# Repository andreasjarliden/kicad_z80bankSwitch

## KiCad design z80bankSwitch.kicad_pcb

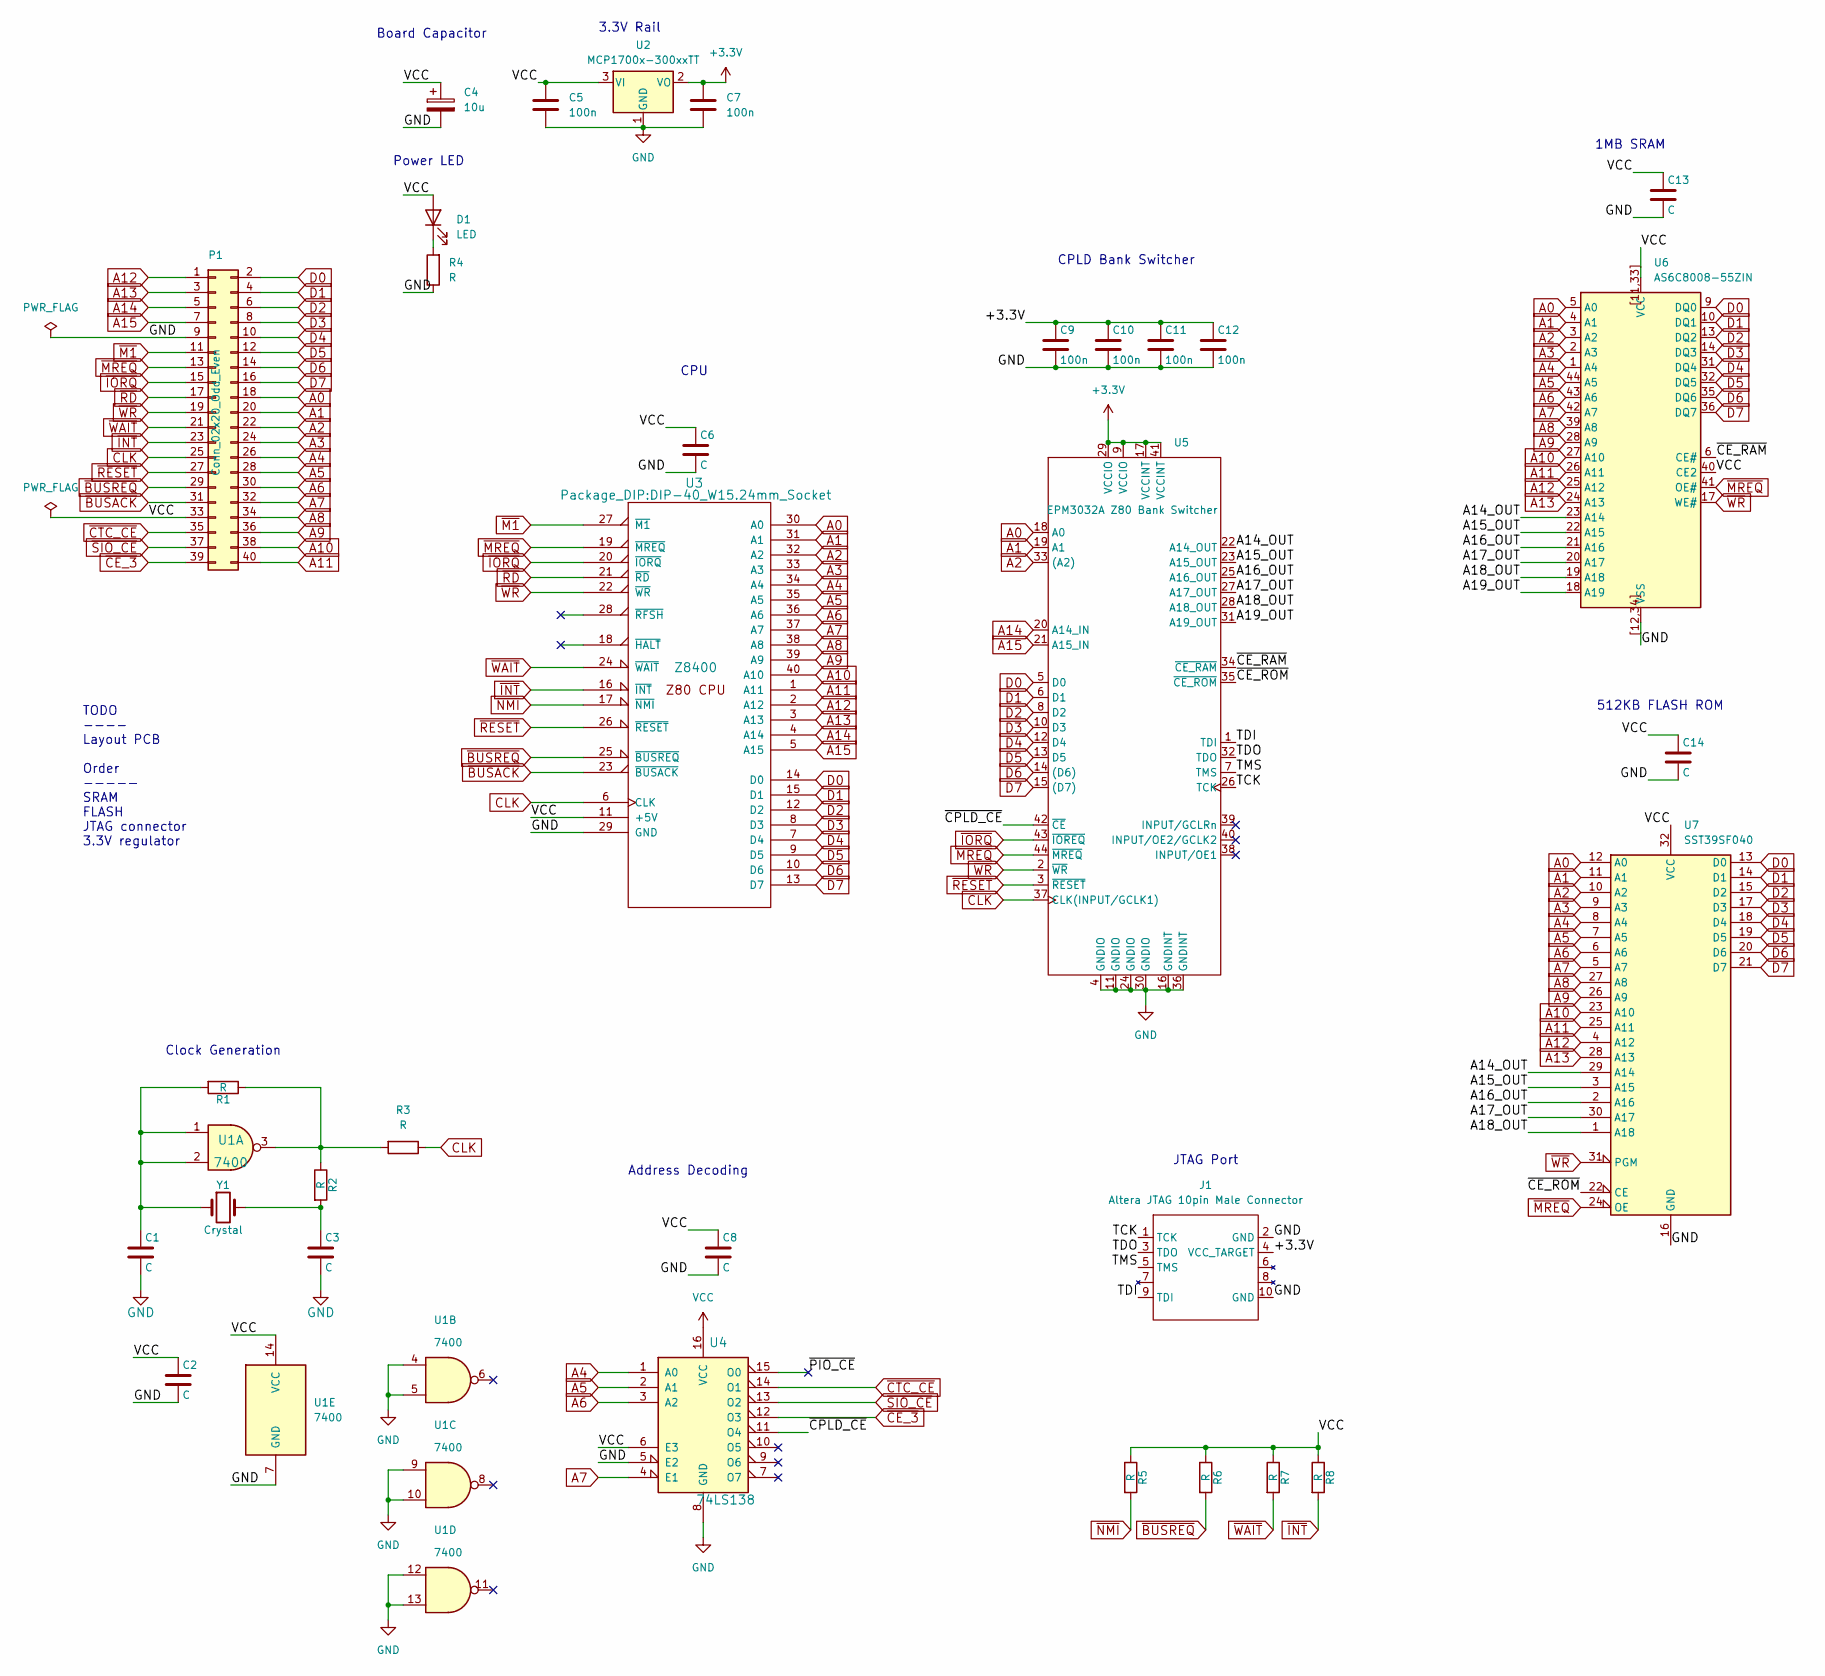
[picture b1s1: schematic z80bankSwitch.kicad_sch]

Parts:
C1, C2, C3, C6, C8, C13, C14: C; C_0805_2012Metric_Pad1.18x1.45mm_HandSolder
C4: 10u; CP_Radial_D10.0mm_P5.00mm
C5, C7, C9, C10, C11, C12: 100n; C_0805_2012Metric_Pad1.18x1.45mm_HandSolder
D1: LED; LED_0805_2012Metric_Pad1.15x1.40mm_HandSolder
J1: Altera JTAG 10pin Male Connector; IDC-Header_2x05_P2.54mm_Vertical
P1: Conn_02x20_Odd_Even; PinHeader_2x20_P2.54mm_Horizontal
R1, R2, R3, R4, R5, R6, R7, R8: R; R_0805_2012Metric_Pad1.20x1.40mm_HandSolder
U1: 7400; DIP-14_W7.62mm_Socket_LongPads
U2: MCP1700x-300xxTT; SOT-23
U3: Z8400; DIP-40_W15.24mm_Socket
U4: 74LS138; DIP-16_W7.62mm_Socket_LongPads
U5: EPM3032A Z80 Bank Switcher; TQFP-44_10x10mm_P0.8mm
U6: AS6C8008-55ZIN; TSOP-II-44_10.16x18.41mm_P0.8mm
U7: SST39SF040; PLCC-32_THT-Socket
Y1: Crystal; Crystal_HC49-4H_Vertical

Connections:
+3.3V: C7.1, C9.1, C10.1, C11.1, C12.1, J1.4 (VCC_TARGET), U2.2 (VO), U5.9 (VCCIO), U5.17 (VCCINT), U5.29 (VCCIO), U5.41 (VCCINT)
/A14_OUT: U5.22 (A14_OUT), U6.23 (A14), U7.29 (A14)
/A15_OUT: U5.23 (A15_OUT), U6.22 (A15), U7.3 (A15)
/A16_OUT: U5.25 (A16_OUT), U6.21 (A16), U7.2 (A16)
/A17_OUT: U5.27 (A17_OUT), U6.20 (A17), U7.30 (A17)
/A18_OUT: U5.28 (A18_OUT), U6.19 (A18), U7.1 (A18)
/A19_OUT: U5.31 (A19_OUT), U6.18 (A19)
/TCK: J1.1 (TCK), U5.26 (TCK)
/TDI: J1.9 (TDI), U5.1 (TDI)
/TDO: J1.3 (TDO), U5.32 (TDO)
/TMS: J1.5 (TMS), U5.7 (TMS)
/~CE_RAM: U5.34 (~CE_RAM), U6.6 (CE#)
/~CE_ROM: U5.35 (~CE_ROM), U7.22 (CE)
/~CPLD_CE: U4.11 (O4), U5.42 (~CE)
/~PIO_CE: U4.15 (O0)
A0: P1.18, U3.30 (A0), U5.18 (A0), U6.5 (A0), U7.12 (A0)
A1: P1.20, U3.31 (A1), U5.19 (A1), U6.4 (A1), U7.11 (A1)
A2: P1.22, U3.32 (A2), U5.33 ((A2)), U6.3 (A2), U7.10 (A2)
A3: P1.24, U3.33 (A3), U6.2 (A3), U7.9 (A3)
A4: P1.26, U3.34 (A4), U4.1 (A0), U6.1 (A4), U7.8 (A4)
A5: P1.28, U3.35 (A5), U4.2 (A1), U6.44 (A5), U7.7 (A5)
A6: P1.30, U3.36 (A6), U4.3 (A2), U6.43 (A6), U7.6 (A6)
A7: P1.32, U3.37 (A7), U4.4 (E1), U6.42 (A7), U7.5 (A7)
A8: P1.34, U3.38 (A8), U6.39 (A8), U7.27 (A8)
A9: P1.36, U3.39 (A9), U6.28 (A9), U7.26 (A9)
A10: P1.38, U3.40 (A10), U6.27 (A10), U7.23 (A10)
A11: P1.40, U3.1 (A11), U6.26 (A11), U7.25 (A11)
A12: P1.1, U3.2 (A12), U6.25 (A12), U7.4 (A12)
A13: P1.3, U3.3 (A13), U6.24 (A13), U7.28 (A13)
A14: P1.5, U3.4 (A14), U5.20 (A14_IN)
A15: P1.7, U3.5 (A15), U5.21 (A15_IN)
CLK: P1.25, R3.1, U3.6 (CLK), U5.37 (CLK(INPUT/GCLK1))
D0: P1.2, U3.14 (D0), U5.5 (D0), U6.9 (DQ0), U7.13 (D0)
D1: P1.4, U3.15 (D1), U5.6 (D1), U6.10 (DQ1), U7.14 (D1)
D2: P1.6, U3.12 (D2), U5.8 (D2), U6.13 (DQ2), U7.15 (D2)
D3: P1.8, U3.8 (D3), U5.10 (D3), U6.14 (DQ3), U7.17 (D3)
D4: P1.10, U3.7 (D4), U5.12 (D4), U6.31 (DQ4), U7.18 (D4)
D5: P1.12, U3.9 (D5), U5.13 (D5), U6.32 (DQ5), U7.19 (D5)
D6: P1.14, U3.10 (D6), U5.14 ((D6)), U6.35 (DQ6), U7.20 (D6)
D7: P1.16, U3.13 (D7), U5.15 ((D7)), U6.36 (DQ7), U7.21 (D7)
GND: C1.2, C2.2, C3.2, C4.2, C5.2, C6.2, C7.2, C8.2, C9.2, C10.2, C11.2, C12.2, C13.2, C14.2, J1.2 (GND), J1.10 (GND), P1.9, R4.1, U1.4, U1.5, U1.7 (GND), U1.9, U1.10, U1.12, U1.13, U2.1 (GND), U3.29 (GND), U4.5 (E2), U4.8 (GND), U5.4 (GNDIO), U5.11 (GNDIO), U5.16 (GNDINT), U5.24 (GNDIO), U5.30 (GNDIO), U5.36 (GNDINT), U6.12 (VSS), U6.34 (VSS), U6.[12,34] (VSS), U7.16 (GND)
unnamed: C1.1, R1.2, U1.1, U1.2, Y1.1
unnamed: C3.1, R2.2, Y1.2
unnamed: D1.1 (K), R4.2
unnamed: R1.1, R2.1, R3.2, U1.3
VCC: C2.1, C4.1, C5.1, C6.1, C8.1, C13.1, C14.1, D1.2 (A), P1.33, R5.1, R6.1, R7.1, R8.1, U1.14 (VCC), U2.3 (VI), U3.11 (+5V), U4.6 (E3), U4.16 (VCC), U6.11 (VCC), U6.33 (VCC), U6.40 (CE2), U6.[11,33] (VCC), U7.32 (VCC)
~BUSACK: P1.31, U3.23 (~BUSACK)
~BUSREQ: P1.29, R6.2, U3.25 (~BUSREQ)
~CE_3: P1.39, U4.12 (O3)
~CTC_CE: P1.35, U4.14 (O1)
~INT: P1.23, R8.2, U3.16 (~INT)
~IORQ: P1.15, U3.20 (~IORQ), U5.43 (~IOREQ)
~M1: P1.11, U3.27 (~M1)
~MREQ: P1.13, U3.19 (~MREQ), U5.44 (~MREQ), U6.41 (OE#), U7.24 (OE)
~NMI: R5.2, U3.17 (~NMI)
~RD: P1.17, U3.21 (~RD)
~RESET: P1.27, U3.26 (~RESET), U5.3 (~RESET)
~SIO_CE: P1.37, U4.13 (O2)
~WAIT: P1.21, R7.2, U3.24 (~WAIT)
~WR: P1.19, U3.22 (~WR), U5.2 (~WR), U6.17 (WE#), U7.31 (PGM)

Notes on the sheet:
TODO ---- Layout PCB Order ----- SRAM FLASH JTAG connector 3.3V regulator
1MB SRAM
Clock Generation
CPLD Bank Switcher
Power LED
CPU
512KB FLASH ROM
3.3V Rail
JTAG Port
Board Capacitor
Address Decoding

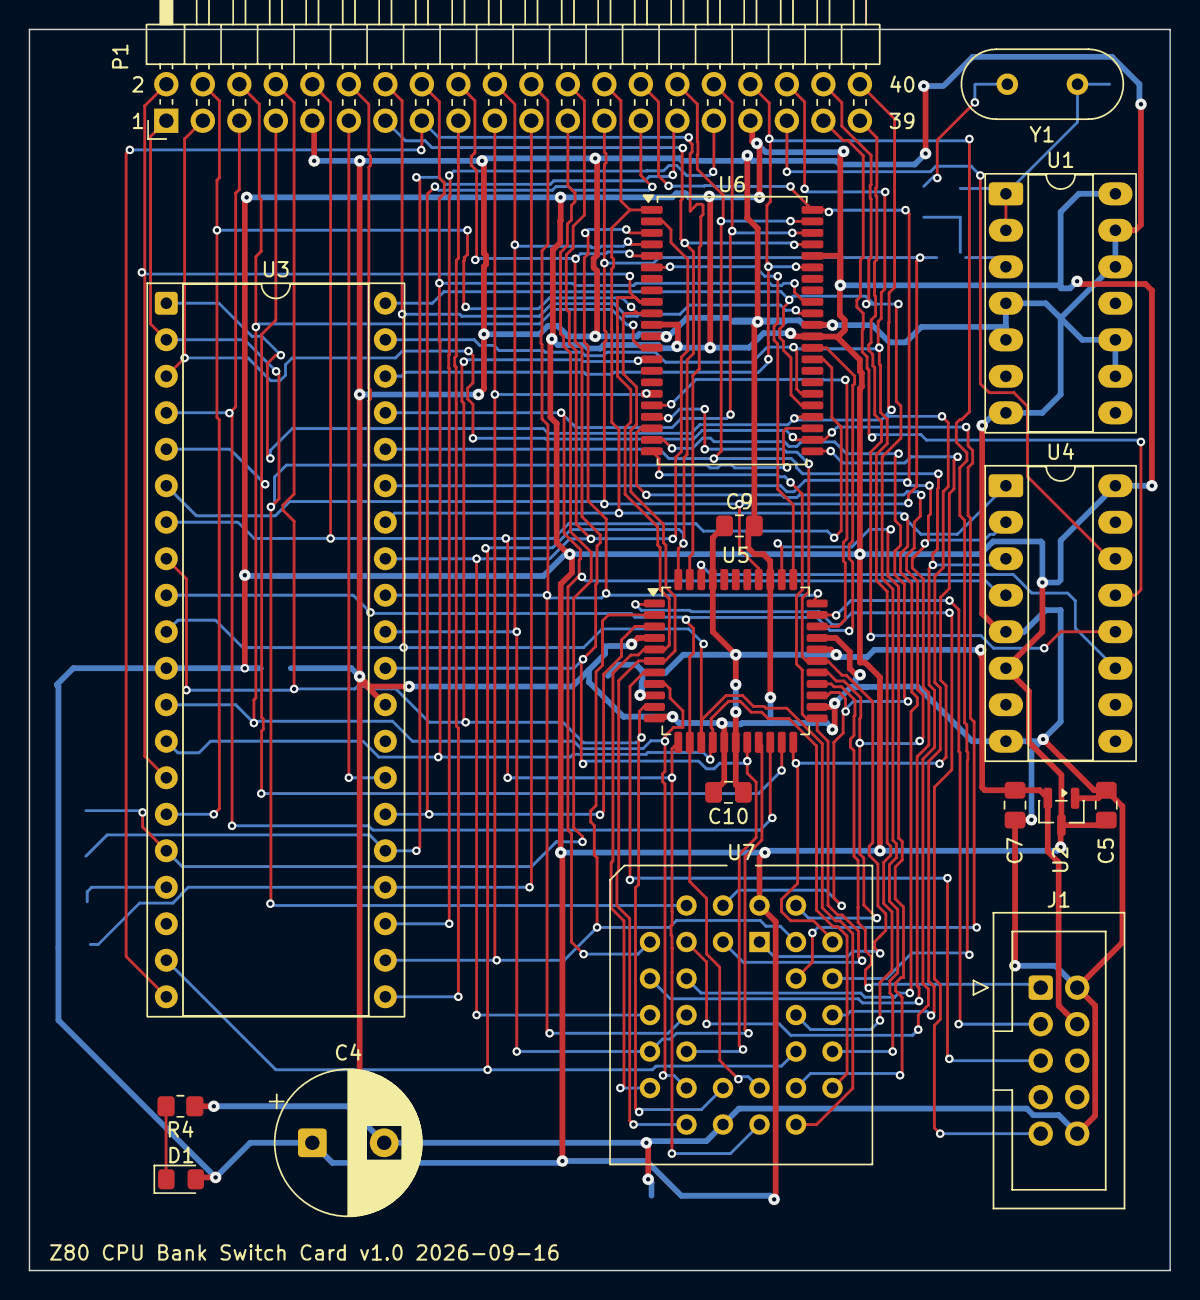
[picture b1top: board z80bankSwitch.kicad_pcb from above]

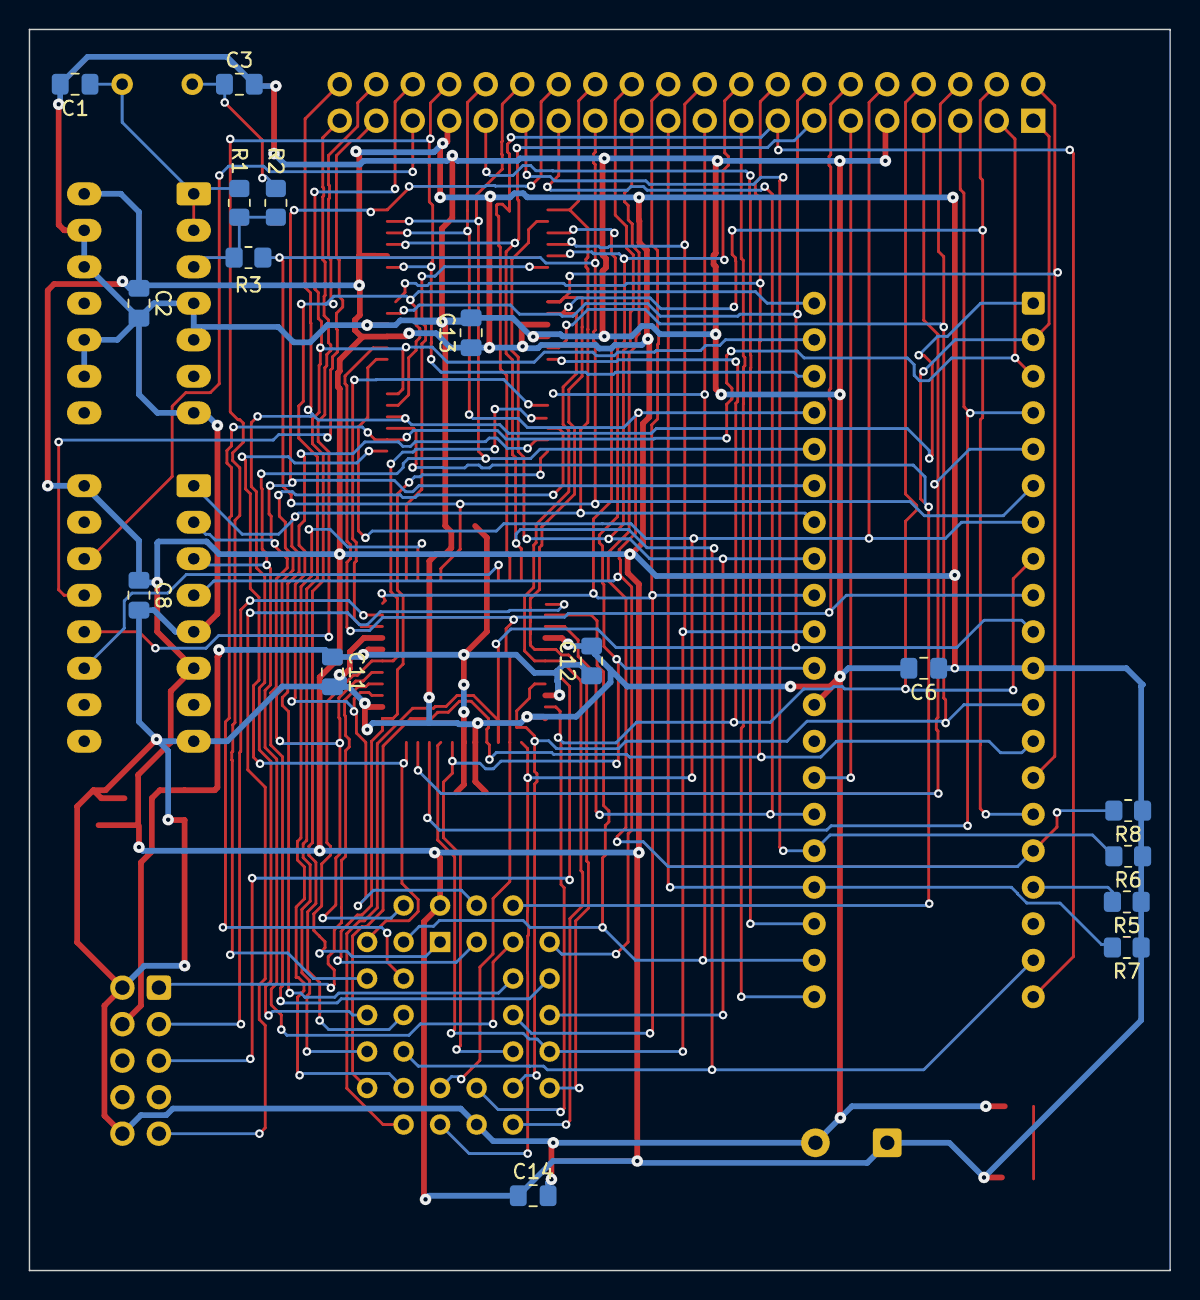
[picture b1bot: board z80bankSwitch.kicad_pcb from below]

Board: 2 copper layers, 79.4 x 86.4 mm, 33 parts (16 on the bottom side), 59 nets.
